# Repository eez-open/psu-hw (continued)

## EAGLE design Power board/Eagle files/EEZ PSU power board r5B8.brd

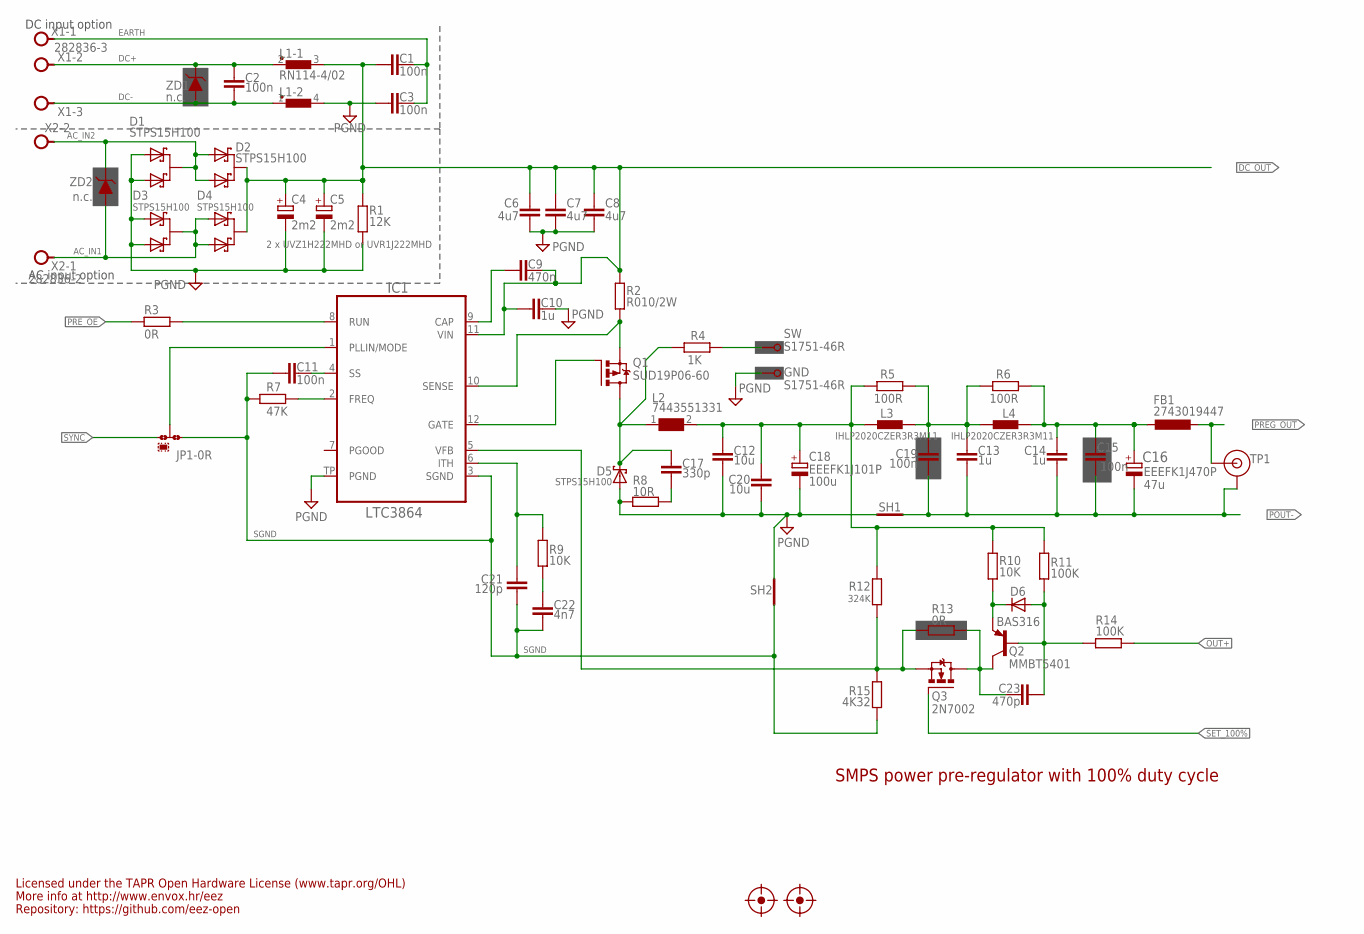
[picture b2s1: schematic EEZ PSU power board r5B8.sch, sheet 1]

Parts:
C1, C2, C3: 100n; C1206
C4, C5: 2m2; ECAP7.5/18
C6, C7, C8: 4u7; C1210
C9: 470n; C0805
C10, C13, C14: 1u; C1206
C11, C15, C19: 100n; C0805
C12, C20: 10u; C1210
C16: EEEFK1J470P; CAPAE830X1050N
C17: 330p; C0805
C18: EEEFK1J101P; PANASONIC_F
C21: 120p; C0805
C22: 4n7; C0805
C23: 470p; C0805
D1, D2, D3, D4: STPS15H100; TO252@1
D5: STPS15H100; TO252
D6: BAS316; SOD323-W
FB1: 2743019447; L1812
GND: S1751-46R
IC1: LTC3864; LTC_05-08-1666
JP1: 0R-JUMPA; A0R-JMP
L1: RN114-4/02; RN114
L2: 7443551331; WE-HCI_1350/1365
L3, L4: IHLP2020CZER3R3M11; IHLP-2020BZ-11
Q1: SUD19P06-60; TO229P990X239-3N
Q2: MMBT5401; SOT23-BEC
Q3: 2N7002; SOT103P240X110-3N
R1: 12K; R1206
R2: R010/2W; R2512
R3, R13: 0R; R0805
R4: 1K; R0805
R5, R6: 100R; R0805
R7: 47K; R0805
R8: 10R; R1206
R9, R10: 10K; R0805
R11, R14: 100K; R0805
R12: 324K; R0805
R15: 4K32; R0805
SH1: Pgnd to Pout- short; SHORT_NOHOLE
SH2: Sgnd to Pgnd short; SHORT_NOHOLE
SW: S1751-46R
TP1: TEST_POINT; TP_1.1MM
U$11, U$12: FIDUCIAL_2; FIDUCIAL_DUAL
X1: 282836-3; TBLOCK5.0_3
X2: 282836-2; TBLOCK5.0_2
ZD1, ZD2: n.c.; DO214AA

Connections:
!SET_100%: Q3.1 (G); also elsewhere on the board
AC_IN1: D3.3 (C), D4.1 (A1), D4.2 (A2), X2.1, ZD2.A (2)
AC_IN2: D1.3 (C), D2.1 (A1), D2.2 (A2), X2.2, ZD2.C (1)
DC+: C2.2, L1.2 (1), X1.2, ZD1.C (1)
DC-: C2.1, L1.1, X1.3, ZD1.A (2)
DC_OUT: C1.2, C4.+, C5.+, C6.1, C7.1, C8.1, C9.2, C10.1, D2.3 (C), D4.3 (C), IC1.11 (VIN), L1.3 (2), R1.1, R2.1; also elsewhere on the board
EARTH: C1.1, C3.2, X1.1
FB: IC1.5 (VFB), Q3.2 (S), R12.2, R13.2, R15.1
GND: C3.1, C4.-, C5.-, C6.2, C7.2, C8.2, C10.2, C12.2, C18.2 (-), C20.2, D1.1 (A1), D1.2 (A2), D3.1 (A1), D3.2 (A2), D5.1 (A), D5.2 (A), GND.P$1, IC1.TP (PGND), L1.4 (2), R1.2, R8.1, SH1.P$2 (GND_B), SH2.P$2 (GND_B); also elsewhere on the board
L_OUT: C12.1, C18.1 (+), C20.1, L2.2, L3.1, R5.1, R10.1, R11.1, R12.1
MODE: IC1.1 (PLLIN/MODE), JP1.2
unnamed: R4.2, SW.P$1
unnamed: D6.C, Q2.E, R10.2
unnamed: C21.1, IC1.6 (ITH), R9.2
unnamed: C22.1, R9.1
unnamed: C9.1, IC1.9 (CAP)
unnamed: IC1.12 (GATE), Q1.1 (G)
unnamed: IC1.2 (FREQ), R7.1
unnamed: C11.2, IC1.4 (SS)
unnamed: C23.1, Q2.C, Q3.3 (D), R13.1
unnamed: C13.1, C19.2, L3.2, L4.1, R5.2, R6.1
unnamed: IC1.8 (RUN), R3.1
unnamed: C17.2, R8.2
unnamed: C23.2, D6.A, Q2.B, R11.2, R14.1
OUT+: R14.2; also elsewhere on the board
POUT-: C13.2, C14.2, C15.2, C16.2, C19.1, SH1.P$1 (GND_A), TP1.GND; also elsewhere on the board
PREG_OUT: FB1.2, TP1.TIP; also elsewhere on the board
PRE_OE: R3.2; also elsewhere on the board
P_OUT: C14.1, C15.1, C16.1, FB1.1, L4.2, R6.2
SENSE: IC1.10 (SENSE), Q1.3 (S), R2.2
SGND: C11.1, C21.2, C22.2, IC1.3 (SGND), JP1.1, R7.2, R15.2, SH2.P$1 (GND_A)
SW: C17.1, D5.3 (C), L2.1, Q1.2 (D), R4.1
SYNC: JP1.3; also elsewhere on the board

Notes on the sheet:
47u
2 x UVZ1H222MHD or UVR1J222MHD
Licensed under the TAPR Open Hardware License (www.tapr.org/OHL)
Repository: https://github.com/eez-open
More info at http://www.envox.hr/eez
SMPS power pre-regulator with 100% duty cycle
100u
DC input option
AC input option

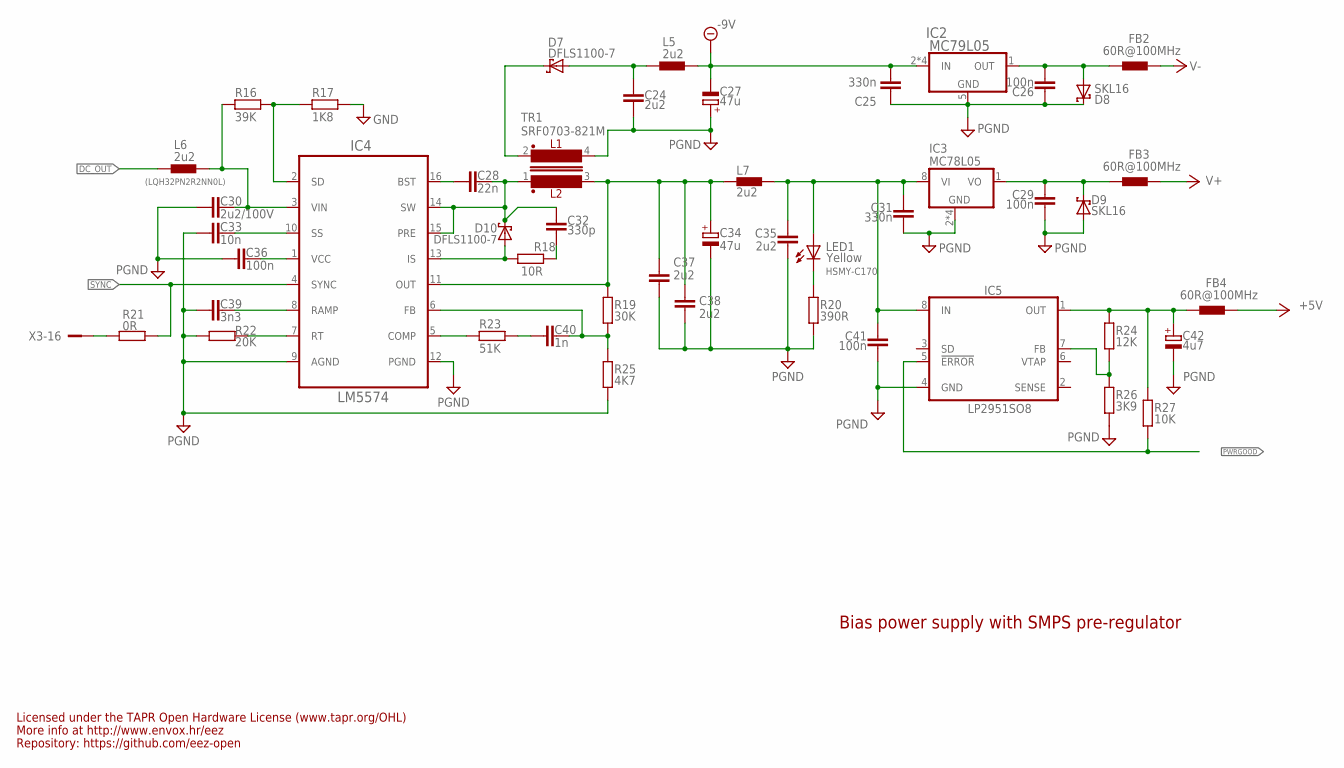
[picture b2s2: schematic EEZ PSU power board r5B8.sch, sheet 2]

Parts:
C24, C35, C37, C38: 2u2; C0805
C25, C31: 330n; C0805
C26, C29, C36, C41: 100n; C0805
C27, C34: 47u; CAPAE660X610N
C28: 22n; C0805
C30: 2u2/100V; C1210
C32: 330p; C0805
C33: 10n; C0805
C39: 3n3; C0805
C40: 1n; C0805
C42: 4u7; EC1206
D7, D10: DFLS1100-7; SOD123
D8, D9: SKL16; SOD123
FB2, FB3, FB4: 60R@100MHz; BEAD0603
IC2: MC79L05; SOIC127P600X173-8N
IC3: MC78L05; SOIC127P600X173-8N
IC4: LM5574; SOP65P640X110-16N
IC5: LP2951SO8; SOIC127P600X175-8N
L5, L6, L7: 2u2; L1210
LED1: HSMY-C170; LED_0805
R16: 39K; R0805
R17: 1K8; R0805
R18: 10R; R1206
R19: 30K; R0805
R20: 390R; R0805
R21: 0R; R0805
R22: 20K; R0805
R23: 51K; R0805
R24: 12K; R0805
R25: 4K7; R0805
R26: 3K9; R0805
R27: 10K; R0805
TR1: SRF0703-821M; SRF0703
X3: SSW-113-02-T-D-RA; FARNELL 1805583

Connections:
+5V: FB4.P$2 (2); also elsewhere on the board
+VNR: C31.1, C35.1, C41.1, IC3.8 (VI), IC5.8 (IN), L7.2, LED1.A
-9V: C25.2, C27.2 (-), IC2.2 (IN), IC2.3 (IN), IC2.6 (IN), IC2.7 (IN), L5.2; also elsewhere on the board
DC_OUT: L6.1; also elsewhere on the board
DC_PREG1: C30.1, IC4.3 (VIN), L6.2, R16.2
GND: C24.2, C25.1, C26.1, C27.1 (+), C29.2, C30.2, C31.2, C33.2, C34.2 (-), C35.2, C36.1, C37.2, C38.2, C39.1, C41.2, C42.-, D8.C, D9.A, IC2.5 (GND), IC3.2 (GND), IC3.3 (GND), IC3.6 (GND), IC3.7 (GND), IC4.9 (AGND), IC4.12 (PGND), IC5.4 (GND), R17.1, R20.2, R22.2, R25.2, R26.2, TR1.4; also elsewhere on the board
IS: D10.A, IC4.13 (IS), R18.1
unnamed: C26.2, D8.A, FB2.P$1 (1), IC2.1 (OUT)
unnamed: C29.1, D9.C, FB3.P$1 (1), IC3.1 (VO)
unnamed: C42.+, FB4.P$1 (1), IC5.1 (OUT), R24.1, R27.1
unnamed: R21.2, X3.16
unnamed: LED1.C, R20.1
unnamed: C32.2, R18.2
unnamed: IC5.7 (FB), R24.2, R26.1
unnamed: C40.2, R23.2
unnamed: C40.1, IC4.6 (FB), R19.2, R25.1
unnamed: C28.2, IC4.16 (BST)
unnamed: IC4.5 (COMP), R23.1
unnamed: IC4.7 (RT), R22.1
unnamed: C36.2, IC4.1 (VCC)
unnamed: C39.2, IC4.8 (RAMP)
unnamed: C33.1, IC4.10 (SS)
unnamed: C24.1, D7.A, L5.1
unnamed: IC4.2 (SD), R16.1, R17.2
PWRGOOD: IC5.5 (!ERROR), R27.2; also elsewhere on the board
SW1: C28.1, C32.1, D10.C, IC4.14 (SW), IC4.15 (PRE), TR1.1
SYNC: IC4.4 (SYNC), R21.1; also elsewhere on the board
V+: FB3.P$2 (2); also elsewhere on the board
V-: FB2.P$2 (2); also elsewhere on the board
VOUT+: C34.1 (+), C37.1, C38.1, IC4.11 (OUT), L7.1, R19.1, TR1.3
VOUT-: D7.C, TR1.2

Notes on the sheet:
(LQH32PN2R2NN0L)
Bias power supply with SMPS pre-regulator
Yellow
Licensed under the TAPR Open Hardware License (www.tapr.org/OHL)
Repository: https://github.com/eez-open
More info at http://www.envox.hr/eez

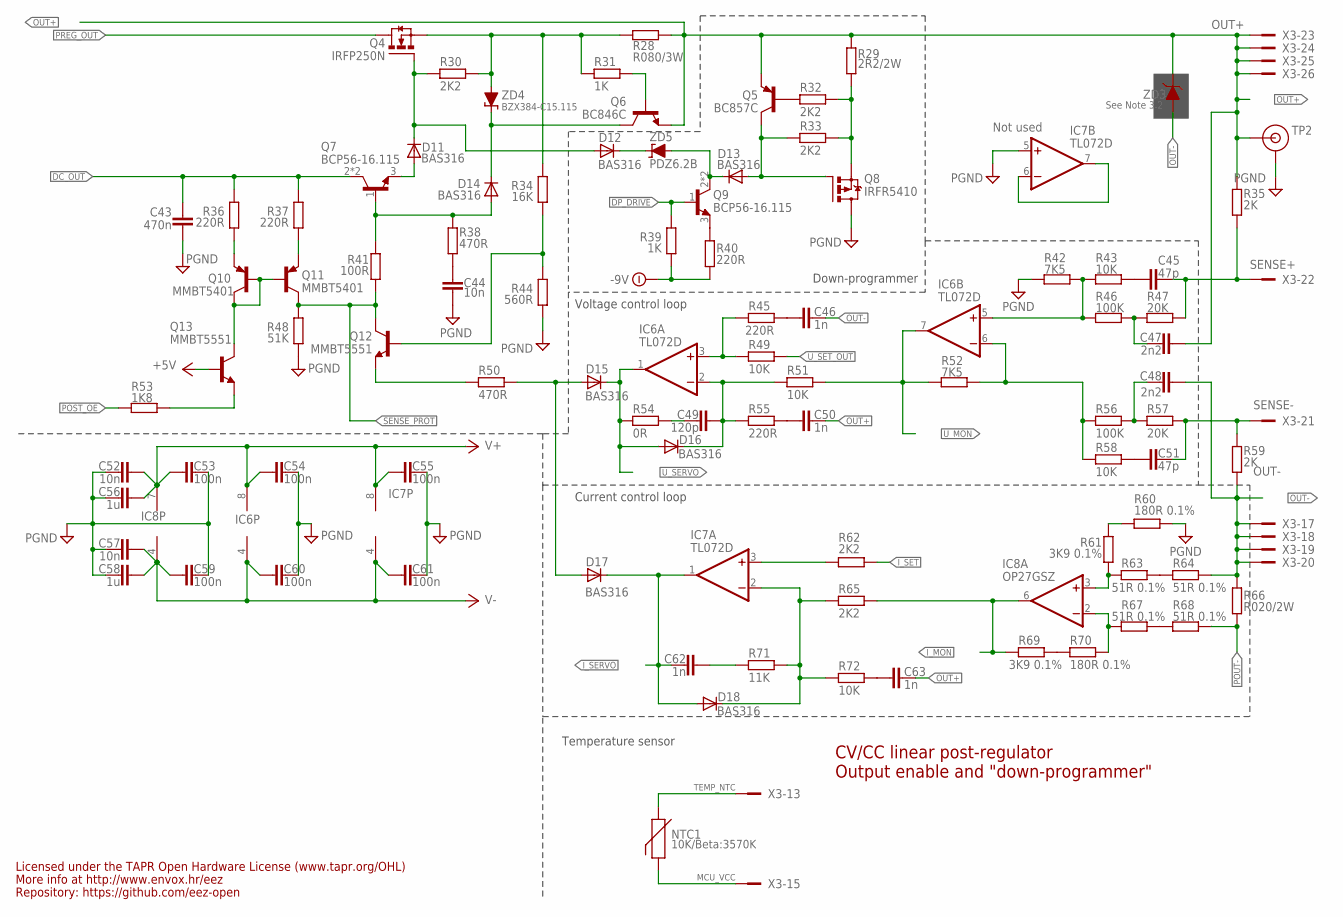
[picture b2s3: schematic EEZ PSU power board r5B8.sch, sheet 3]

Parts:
C43: 470n; C1812
C44, C52, C57: 10n; C0805
C45, C51: 47p; C0805
C46, C50, C62, C63: 1n; C0805
C47, C48: 2n2; C0805
C49: 120p; C0805
C53, C54, C55, C59, C60, C61: 100n; C0603
C56, C58: 1u; C0805
D11, D12, D13, D14, D15, D16, D17, D18: BAS316; SOD323-W
IC6, IC7: TL072D; SOIC127P600X173-8N
IC8: OP27GSZ; SOIC127P600X173-8N
NTC1: 10K/Beta:3570K; R_0204/5+0805
Q4: IRFP250N; TO247BH-CLR
Q5: BC857C; SOT23-BEC
Q6: BC846C; SOT23-BEC
Q7, Q9: BCP56-16.115; SOT230P700X180-4N
Q8: IRFR5410; TO229P990X239-3N
Q10, Q11: MMBT5401; SOT23-BEC
Q12, Q13: MMBT5551; SOT23-BEC
R28: R080/3W; R2512
R29: 2R2/2W; R2512
R30, R32, R33, R62, R65: 2K2; R0805
R31, R39: 1K; R0805
R34: 16K; R0805
R35, R59: 2K; R0805
R36, R37, R40, R45, R55: 220R; R0805
R38, R50: 470R; R0805
R41: 100R; R0805
R42, R52: 7K5; R0805
R43, R49, R51, R58, R72: 10K; R0805
R44: 560R; R0805
R46, R56: 100K; R0805
R47, R57: 20K; R0805
R48: 51K; R0805
R53: 1K8; R0805
R54: 0R; R0805
R60, R70: 180R 0.1%; R0805
R61, R69: 3K9 0.1%; R0805
R63, R64, R67, R68: 51R 0.1%; R0805
R66: R020/2W; R2512
R71: 11K; R0805
TP2: TEST_POINT; TP_1.1MM
X3: SSW-113-02-T-D-RA; FARNELL 1805583
ZD3: See Note 3.2; DO214AA
ZD4: BZX384-C15.115; SOD323-W
ZD5: PDZ6.2B; SOD323-W

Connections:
!DP_DRIVE: Q9.1 (B), R39.1; also elsewhere on the board
+5V: Q13.B; also elsewhere on the board
-9V: R39.2, R40.2; also elsewhere on the board
DC_OUT: C43.1, Q7.2 (C), Q7.4 (C), R36.2, R37.2; also elsewhere on the board
GND: C43.2, C44.2, C52.1, C53.2, C54.1, C55.1, C56.1, C57.1, C58.1, C59.2, C60.1, C61.1, IC7.5 (+IN), Q8.2 (D), R42.1, R44.1, R48.1, R60.1, TP2.GND; also elsewhere on the board
ISENSE+: IC8.3 (+IN), R61.2, R63.2
ISENSE-: IC8.2 (-IN), R67.2, R70.1
I_MON: IC8.6 (OUT), R65.1, R69.2; also elsewhere on the board
I_SERVO: C62.2, D17.C, D18.A, IC7.1 (OUT); also elsewhere on the board
I_SET: R62.1; also elsewhere on the board
MCU_VCC: NTC1.2, NTC1.2.1, X3.15
unnamed: Q9.3 (E), R40.1
unnamed: Q5.B, R32.2
unnamed: C45.2, R43.1
unnamed: R63.1, R64.2
unnamed: C51.2, R58.1
unnamed: R67.1, R68.2
unnamed: R69.1, R70.2
unnamed: R60.2, R61.1
unnamed: IC7.6 (-IN), IC7.7 (OUT)
unnamed: C48.1, R56.2, R57.1
unnamed: C49.2, R54.1
unnamed: C63.2, R72.1
unnamed: C46.2, R45.1
unnamed: C50.2, R55.1
unnamed: IC6.3 (+IN), R45.2, R49.2
unnamed: C49.1, D16.C, IC6.2 (-IN), R51.2, R55.2
unnamed: D18.C, IC7.2 (-IN), R65.2, R71.2, R72.2
unnamed: Q12.B, R34.1, R44.2
unnamed: IC7.3 (+IN), R62.2
unnamed: D15.A, D17.A, R50.1
unnamed: D11.C, D12.A, Q4.G, R30.1
unnamed: D11.A, Q7.3 (E)
unnamed: D14.A, Q7.1 (B), R38.2, R41.1
unnamed: C44.1, R38.1
unnamed: C47.1, R46.2, R47.1
unnamed: D14.C, Q6.C, ZD4.C
unnamed: D12.C, ZD5.C
unnamed: Q12.E, R50.2
unnamed: Q8.3 (S), R29.1, R32.1, R33.1
unnamed: D13.A, Q5.C, Q8.1 (G), R33.2
unnamed: IC6.5 (+IN), R42.2, R43.2, R46.1
unnamed: IC6.6 (-IN), R52.2, R56.1, R58.2
unnamed: C62.1, R71.1
unnamed: Q11.E, R37.1
unnamed: Q10.E, R36.1
unnamed: Q13.E, R53.2
unnamed: Q6.B, R31.1
OUT+: C47.2, C50.1, C63.1, Q5.E, Q6.E, R28.2, R29.2, R35.1, TP2.TIP, X3.23, X3.24, X3.25, X3.26, ZD3.C (1); also elsewhere on the board
OUT-: C46.1, C48.2, R59.2, R64.1, R66.1, X3.17, X3.18, X3.19, X3.20, ZD3.A (2); also elsewhere on the board
POST_OE: R53.1; also elsewhere on the board
POUT-: R66.2, R68.1; also elsewhere on the board
PREG_OUT: Q4.D; also elsewhere on the board
Q4_OUT: Q4.S, R28.1, R30.2, R31.2, R34.2, ZD4.A
Q7C: Q10.B, Q10.C, Q11.B, Q13.C
Q9C: D13.C, Q9.2 (C), Q9.4 (C), ZD5.A
SENSE+: C45.1, R35.2, R47.2, X3.22; also elsewhere on the board
SENSE-: C51.1, R57.2, R59.1, X3.21; also elsewhere on the board
SENSE_PROT: Q11.C, Q12.C, R41.2, R48.2; also elsewhere on the board
TEMP_NTC: NTC1.1, NTC1.1.1, X3.13
U_MON: IC6.7 (OUT), R51.1, R52.1; also elsewhere on the board
U_SERVO: D15.C, D16.A, IC6.1 (OUT), R54.2; also elsewhere on the board
U_SET_OUT: R49.1; also elsewhere on the board
V+: C52.2, C53.1, C54.2, C55.2, C56.2, IC6.8 (V+), IC7.8 (V+), IC8.7 (V+); also elsewhere on the board
V-: C57.2, C58.2, C59.1, C60.2, C61.2, IC6.4 (V-), IC7.4 (V-), IC8.4 (V-); also elsewhere on the board

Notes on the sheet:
Current control loop
Voltage control loop
CV/CC linear post-regulator
Output enable and "down-programmer"
Down-programmer
Not used
Licensed under the TAPR Open Hardware License (www.tapr.org/OHL)
Repository: https://github.com/eez-open
More info at http://www.envox.hr/eez
Temperature sensor

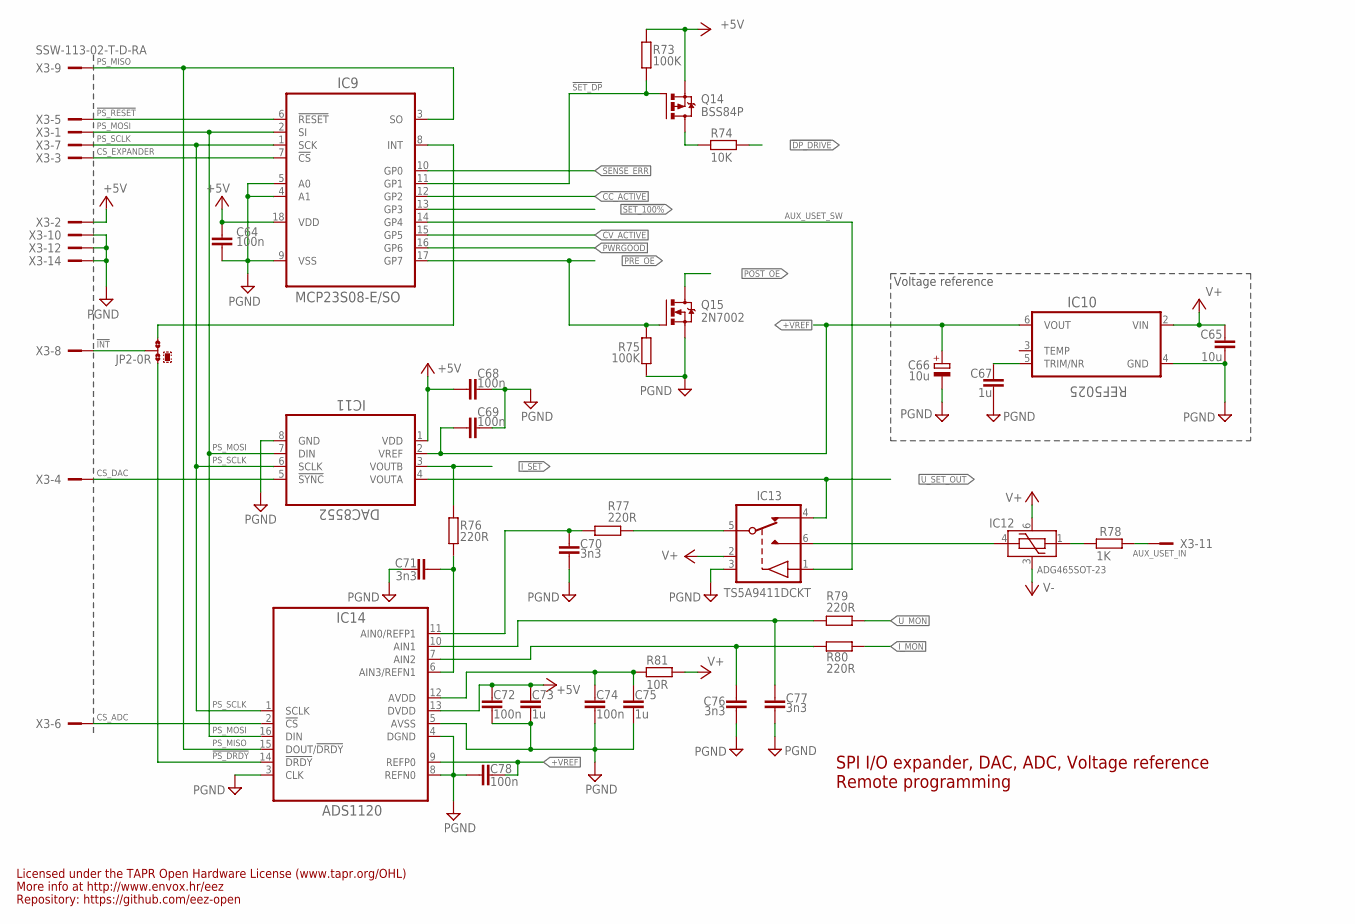
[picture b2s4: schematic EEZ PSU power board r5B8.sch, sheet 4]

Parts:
C64, C68, C69, C72, C74, C78: 100n; C0603
C65: 10u; C1206
C66: 10u; EC1206
C67, C73, C75: 1u; C0805
C70, C71, C76, C77: 3n3; C0805
IC9: MCP23S08-E/SO; SOIC127P1030X265-18N
IC10: REF5025; SOIC127P600X175-8N
IC11: DAC8552; DGK8-M
IC12: ADG465SOT-23; SOT95P280X145-6N
IC13: TS5A9411DCKT; SOT65P210X110-6N
IC14: ADS1120; PW(R-PDSO-G16)
JP2: 0R-JUMPA; A0R-JMP
Q14: BSS84P; SOT95P237X112-3N
Q15: 2N7002; SOT103P240X110-3N; MPN 2N7002-7-F
R73, R75: 100K; R0805
R74: 10K; R0805
R76, R77, R79, R80: 220R; R0805
R78: 1K; R0805
R81: 10R; R0805
X3: SSW-113-02-T-D-RA; FARNELL 1805583

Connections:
!DP_DRIVE: R74.1; also elsewhere on the board
!INT: JP2.2, X3.8
!PS_DRDY: IC14.14 (!DRDY), JP2.3
!PS_RESET: IC9.6 (!RESET), X3.5
!SET_100%: IC9.13 (GP3); also elsewhere on the board
!SET_DP: IC9.11 (GP1), Q14.1 (G), R73.2
+5V: C64.1, C68.2, C72.2, C73.2, IC9.18 (VDD), IC11.1 (VDD), IC14.13 (DVDD), Q14.2 (S), R73.1, X3.2; also elsewhere on the board
+VREF: C66.+, C69.2, C78.2, IC10.6 (VOUT), IC11.2 (VREF), IC14.9 (REFP0)
AUX_USET_IN: R78.2, X3.11
AUX_USET_SW: IC9.14 (GP4), IC13.1 (IN)
CC_ACTIVE: IC9.12 (GP2); also elsewhere on the board
CS_ADC: IC14.2 (!CS), X3.6
CS_DAC: IC11.5 (!SYNC), X3.4
CS_EXPANDER: IC9.7 (!CS), X3.3
CV_ACTIVE: IC9.15 (GP5); also elsewhere on the board
DP_LED: Q14.3 (D), R74.2
GND: C64.2, C65.2, C66.-, C67.2, C68.1, C69.1, C70.1, C71.2, C72.1, C73.1, C74.1, C75.1, C76.1, C77.1, C78.1, IC9.4 (A1), IC9.5 (A0), IC9.9 (VSS), IC10.4 (GND), IC11.8 (GND), IC13.3 (GND), IC14.3 (CLK), IC14.4 (DGND), IC14.5 (AVSS), IC14.8 (REFN0), Q15.2 (S), R75.1, X3.10, X3.12, X3.14; also elsewhere on the board
INT_EXP: IC9.8 (INT), JP2.1
I_MON: R80.1; also elsewhere on the board
I_SET: IC11.3 (VOUTB), R76.1; also elsewhere on the board
unnamed: IC12.4 (VS), IC13.6 (S1)
unnamed: C67.1, IC10.5 (TRIM/NR)
unnamed: IC12.1 (VD), R78.1
unnamed: C77.2, IC14.10 (AIN1), R79.2
unnamed: C70.2, IC14.11 (AIN0/REFP1), R77.2
unnamed: C74.2, C75.2, IC14.12 (AVDD), R81.2
unnamed: C71.1, IC14.6 (AIN3/REFN1), R76.2
unnamed: C76.2, IC14.7 (AIN2), R80.2
POST_OE: Q15.3 (D); also elsewhere on the board
PRE_OE: IC9.17 (GP7), Q15.1 (G), R75.2; also elsewhere on the board
PS_MISO: IC9.3 (SO), IC14.15 (DOUT/!DRDY), X3.9
PS_MOSI: IC9.2 (SI), IC11.7 (DIN), IC14.16 (DIN), X3.1
PS_SCLK: IC9.1 (SCK), IC11.6 (SCLK), IC14.1 (SCLK), X3.7
PWRGOOD: IC9.16 (GP6); also elsewhere on the board
SENSE_ERR: IC9.10 (GP0); also elsewhere on the board
U_MON: R79.1; also elsewhere on the board
U_SET: IC13.5 (D), R77.1
U_SET_OUT: IC11.4 (VOUTA), IC13.4 (S2); also elsewhere on the board
V+: C65.1, IC10.2 (VIN), IC12.6 (VDD), IC13.2 (VDD), R81.1; also elsewhere on the board
V-: IC12.3 (VSS); also elsewhere on the board

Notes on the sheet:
SPI I/O expander, DAC, ADC, Voltage reference
Voltage reference
Licensed under the TAPR Open Hardware License (www.tapr.org/OHL)
Repository: https://github.com/eez-open
More info at http://www.envox.hr/eez
Remote programming

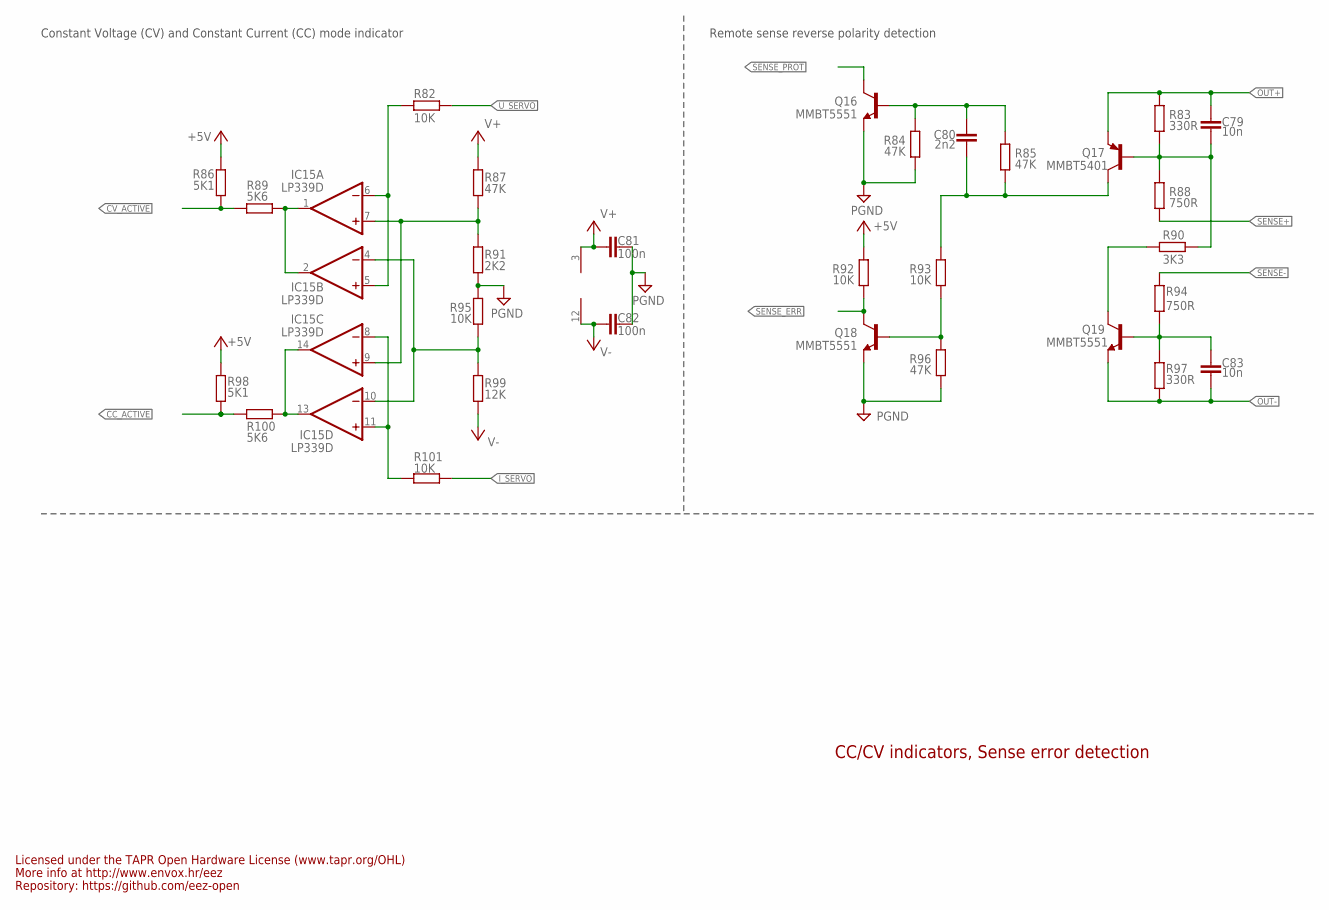
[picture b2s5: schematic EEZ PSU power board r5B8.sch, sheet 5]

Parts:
C79, C83: 10n; C0805
C80: 2n2; C0805
C81, C82: 100n; C0603
IC15: LP339D; SOIC127P600X175-14N
Q16, Q18, Q19: MMBT5551; SOT23-BEC
Q17: MMBT5401; SOT23-BEC
R82, R92, R93, R95, R101: 10K; R0805
R83, R97: 330R; R0805
R84, R85, R87, R96: 47K; R0805
R86, R98: 5K1; R0805
R88, R94: 750R; R0805
R89, R100: 5K6; R0805
R90: 3K3; R0805
R91: 2K2; R0805
R99: 12K; R0805

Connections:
+5V: R86.2, R92.2, R98.2; also elsewhere on the board
CC_ACTIVE: R98.1, R100.2; also elsewhere on the board
CV_ACTIVE: R86.1, R89.2; also elsewhere on the board
GND: C81.1, C82.1, Q16.E, Q18.E, R84.1, R91.1, R95.2, R96.1; also elsewhere on the board
I_SERVO: R101.1; also elsewhere on the board
unnamed: C79.2, Q17.B, R83.1, R88.2, R90.2
unnamed: Q18.B, R93.1, R96.2
unnamed: C80.2, Q17.C, R85.1, R93.2
unnamed: IC15.1 (OUT), IC15.2 (OUT), R89.1
unnamed: Q19.C, R90.1
unnamed: IC15.13 (OUT), IC15.14 (OUT), R100.1
unnamed: C83.1, Q19.B, R94.1, R97.2
unnamed: C80.1, Q16.B, R84.2, R85.2
unnamed: IC15.5 (+IN), IC15.6 (-IN), R82.2
unnamed: IC15.8 (-IN), IC15.11 (+IN), R101.2
unnamed: IC15.7 (+IN), IC15.9 (+IN), R87.1, R91.2
unnamed: IC15.4 (-IN), IC15.10 (-IN), R95.1, R99.2
OUT+: C79.1, Q17.E, R83.2; also elsewhere on the board
OUT-: C83.2, Q19.E, R97.1; also elsewhere on the board
SENSE+: R88.1; also elsewhere on the board
SENSE-: R94.2; also elsewhere on the board
SENSE_ERR: Q18.C, R92.1; also elsewhere on the board
SENSE_PROT: Q16.C; also elsewhere on the board
U_SERVO: R82.1; also elsewhere on the board
V+: C81.2, IC15.3 (V+), R87.2; also elsewhere on the board
V-: C82.2, IC15.12 (GND), R99.1; also elsewhere on the board

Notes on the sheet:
Constant Voltage (CV) and Constant Current (CC) mode indicator
CC/CV indicators, Sense error detection
Licensed under the TAPR Open Hardware License (www.tapr.org/OHL)
Repository: https://github.com/eez-open
More info at http://www.envox.hr/eez
Remote sense reverse polarity detection

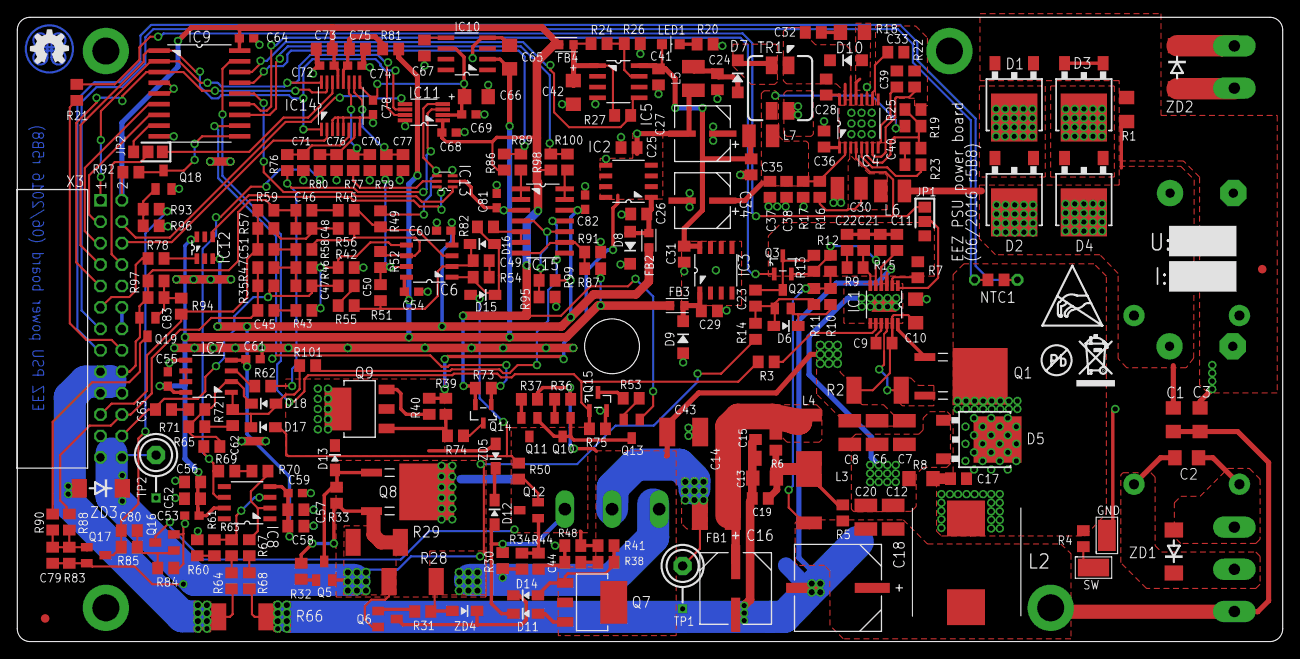
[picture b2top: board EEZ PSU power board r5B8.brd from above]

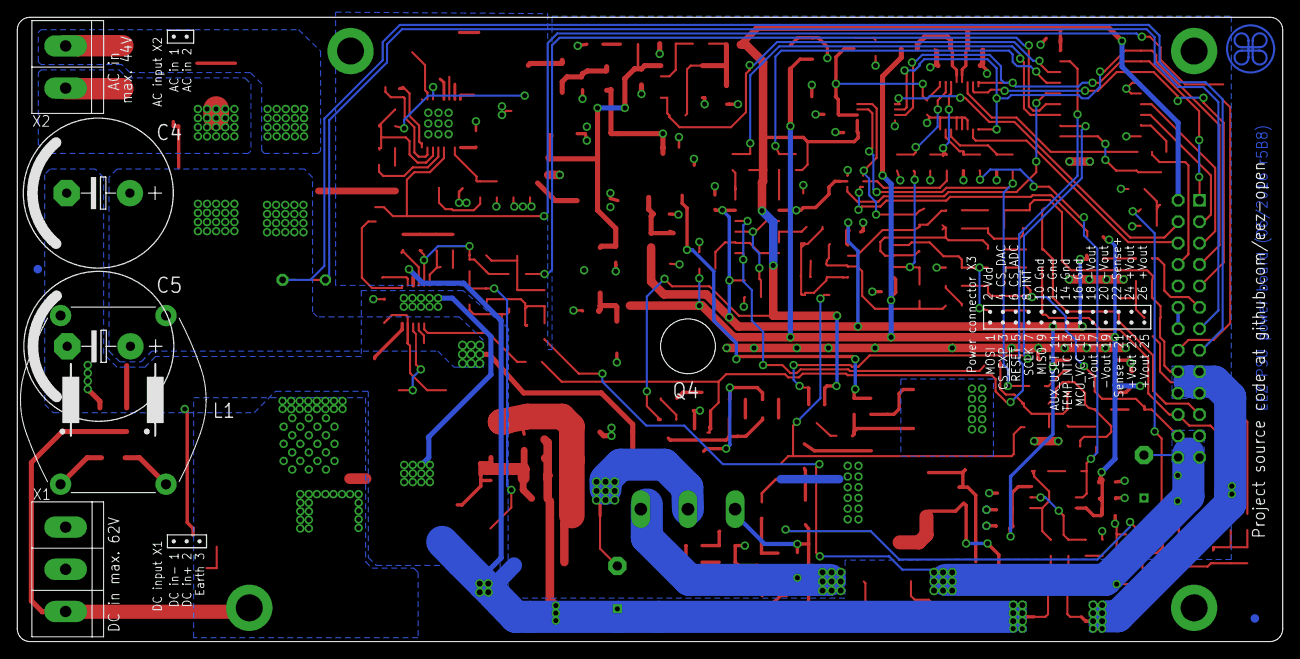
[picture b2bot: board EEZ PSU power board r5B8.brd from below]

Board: 3 copper layers, 150.0 x 74.0 mm, 272 parts (5 on the bottom side), 156 nets.

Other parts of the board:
EEZ_SIGNATURE: SIGNATURESMALL; SIGNATURE_5MM
U$2: RECYCLE_BIN1/8
U$3: PB_SMALL
U$4: ESD_SYMBOL
